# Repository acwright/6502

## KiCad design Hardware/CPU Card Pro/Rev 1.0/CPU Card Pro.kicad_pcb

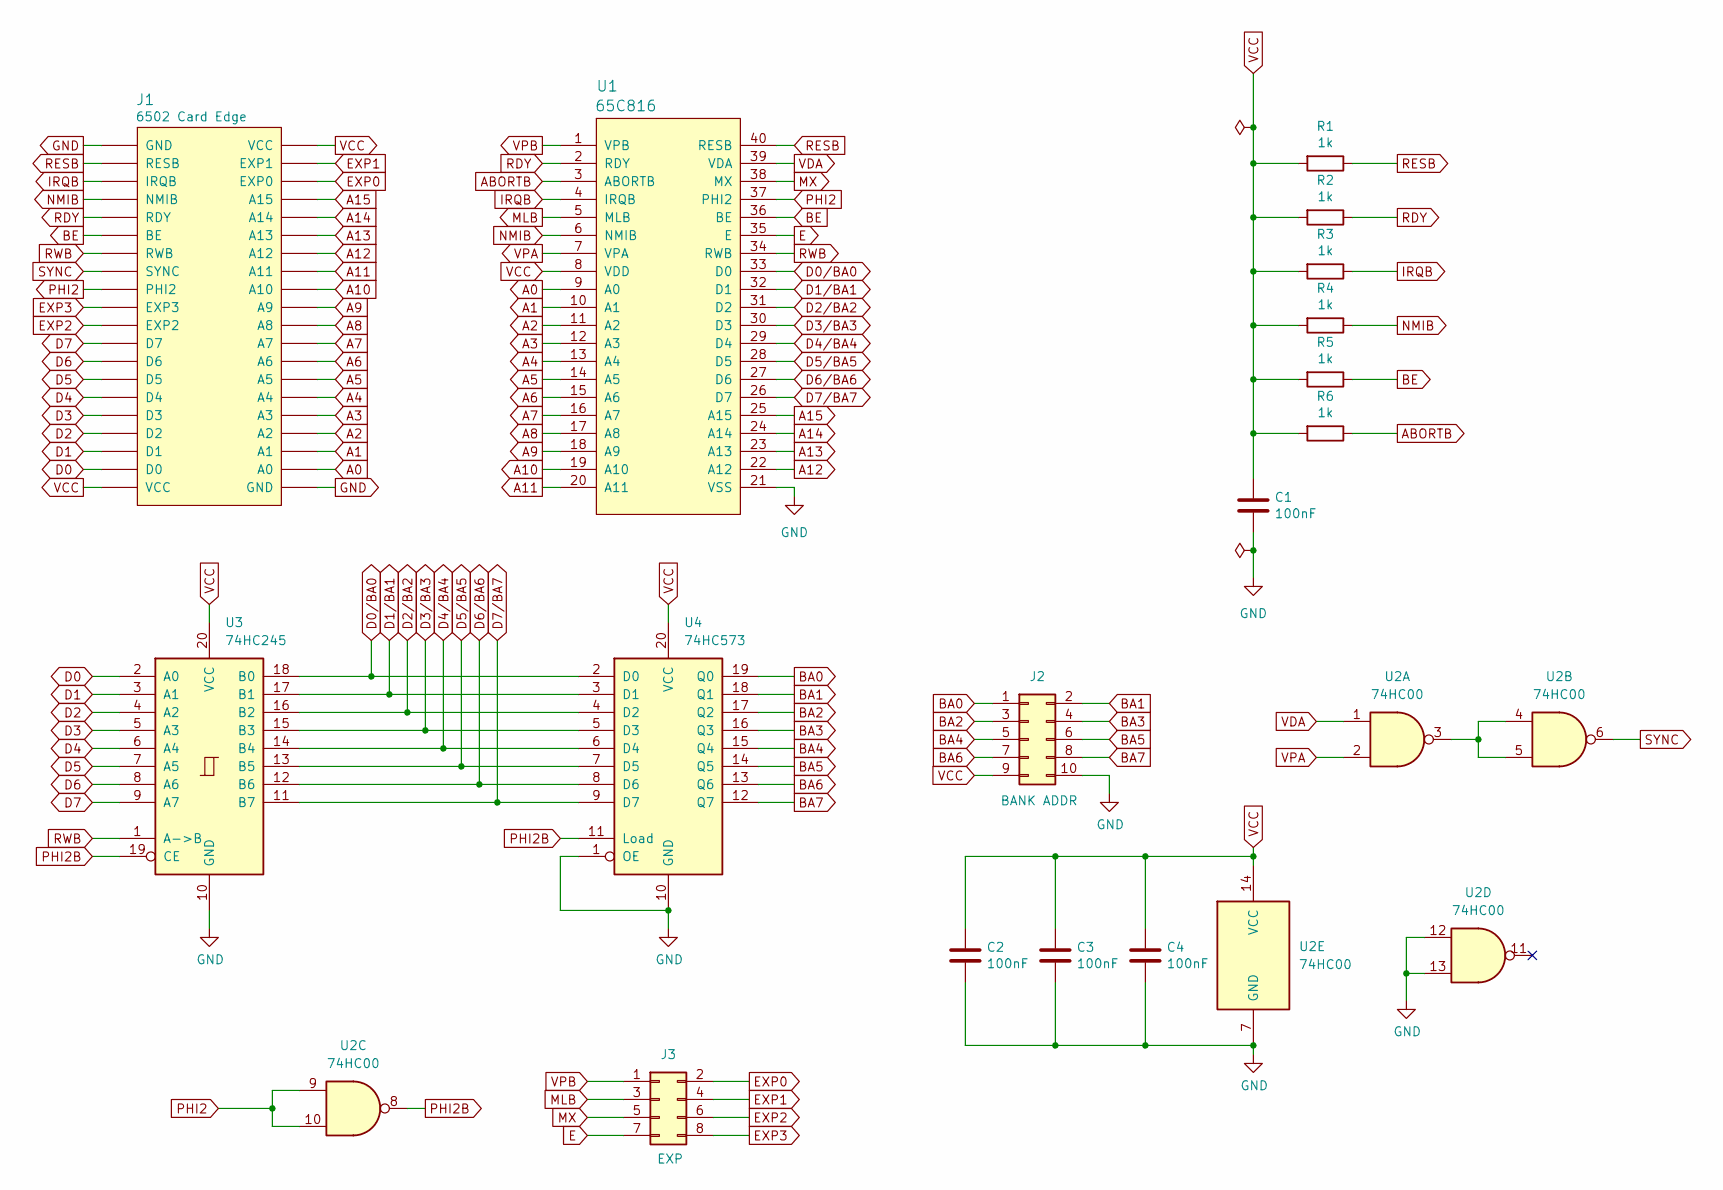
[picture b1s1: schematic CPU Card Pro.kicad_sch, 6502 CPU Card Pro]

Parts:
C1, C2, C3, C4: 100nF; C_0805_2012Metric; LCSC C49678
J1: 6502 Card Edge
J2: BANK ADDR; PinHeader_2x05_P2.54mm_Vertical
J3: EXP; PinHeader_2x04_P2.54mm_Vertical
R1, R2, R3, R4, R5, R6: 1k; R_0805_2012Metric; LCSC C17513
U1: 65C816; DIP-40_W15.24mm_Socket_LongPads
U2: 74HC00; SOIC-14_3.9x8.7mm_P1.27mm; LCSC C5586
U3: 74HC245; TSSOP-20_4.4x6.5mm_P0.65mm; LCSC C5626
U4: 74HC573; SOIC-20W_7.5x12.8mm_P1.27mm; LCSC C5608

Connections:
A0: J1.A0, U1.9 (A0)
A1: J1.A1, U1.10 (A1)
A2: J1.A2, U1.11 (A2)
A3: J1.A3, U1.12 (A3)
A4: J1.A4, U1.13 (A4)
A5: J1.A5, U1.14 (A5)
A6: J1.A6, U1.15 (A6)
A7: J1.A7, U1.16 (A7)
A8: J1.A8, U1.17 (A8)
A9: J1.A9, U1.18 (A9)
A10: J1.A10, U1.19 (A10)
A11: J1.A11, U1.20 (A11)
A12: J1.A12, U1.22 (A12)
A13: J1.A13, U1.23 (A13)
A14: J1.A14, U1.24 (A14)
A15: J1.A15, U1.25 (A15)
ABORTB: R6.1, U1.3 (ABORTB)
BA0: J2.1, U4.19 (Q0)
BA1: J2.2, U4.18 (Q1)
BA2: J2.3, U4.17 (Q2)
BA3: J2.4, U4.16 (Q3)
BA4: J2.5, U4.15 (Q4)
BA5: J2.6, U4.14 (Q5)
BA6: J2.7, U4.13 (Q6)
BA7: J2.8, U4.12 (Q7)
BE: J1.BE, R5.1, U1.36 (BE)
D0: J1.D0, U3.2 (A0)
D0/BA0: U1.33 (D0), U3.18 (B0), U4.2 (D0)
D1: J1.D1, U3.3 (A1)
D1/BA1: U1.32 (D1), U3.17 (B1), U4.3 (D1)
D2: J1.D2, U3.4 (A2)
D2/BA2: U1.31 (D2), U3.16 (B2), U4.4 (D2)
D3: J1.D3, U3.5 (A3)
D3/BA3: U1.30 (D3), U3.15 (B3), U4.5 (D3)
D4: J1.D4, U3.6 (A4)
D4/BA4: U1.29 (D4), U3.14 (B4), U4.6 (D4)
D5: J1.D5, U3.7 (A5)
D5/BA5: U1.28 (D5), U3.13 (B5), U4.7 (D5)
D6: J1.D6, U3.8 (A6)
D6/BA6: U1.27 (D6), U3.12 (B6), U4.8 (D6)
D7: J1.D7, U3.9 (A7)
D7/BA7: U1.26 (D7), U3.11 (B7), U4.9 (D7)
E: J3.7, U1.35 (E)
EXP0: J1.EXP0, J3.2
EXP1: J1.EXP1, J3.4
EXP2: J1.EXP2, J3.6
EXP3: J1.EXP3, J3.8
GND: C1.2, C2.2, C3.2, C4.2, J1.GND, J2.10, U1.21 (VSS), U2.7 (GND), U2.12, U2.13, U3.10 (GND), U4.1 (OE), U4.10 (GND)
IRQB: J1.IRQB, R3.1, U1.4 (IRQB)
MLB: J3.3, U1.5 (MLB)
MX: J3.5, U1.38 (MX)
NMIB: J1.NMIB, R4.1, U1.6 (NMIB)
unnamed: U2.3, U2.4, U2.5
PHI2: J1.PHI2, U1.37 (PHI2), U2.9, U2.10
PHI2B: U2.8, U3.19 (CE), U4.11 (Load)
RDY: J1.RDY, R2.1, U1.2 (RDY)
RESB: J1.RESB, R1.1, U1.40 (RESB)
RWB: J1.RWB, U1.34 (RWB), U3.1 (A->B)
SYNC: J1.SYNC, U2.6
VCC: C1.1, C2.1, C3.1, C4.1, J1.VCC, J2.9, R1.2, R2.2, R3.2, R4.2, R5.2, R6.2, U1.8 (VDD), U2.14 (VCC), U3.20 (VCC), U4.20 (VCC)
VDA: U1.39 (VDA), U2.1
VPA: U1.7 (VPA), U2.2
VPB: J3.1, U1.1 (VPB)

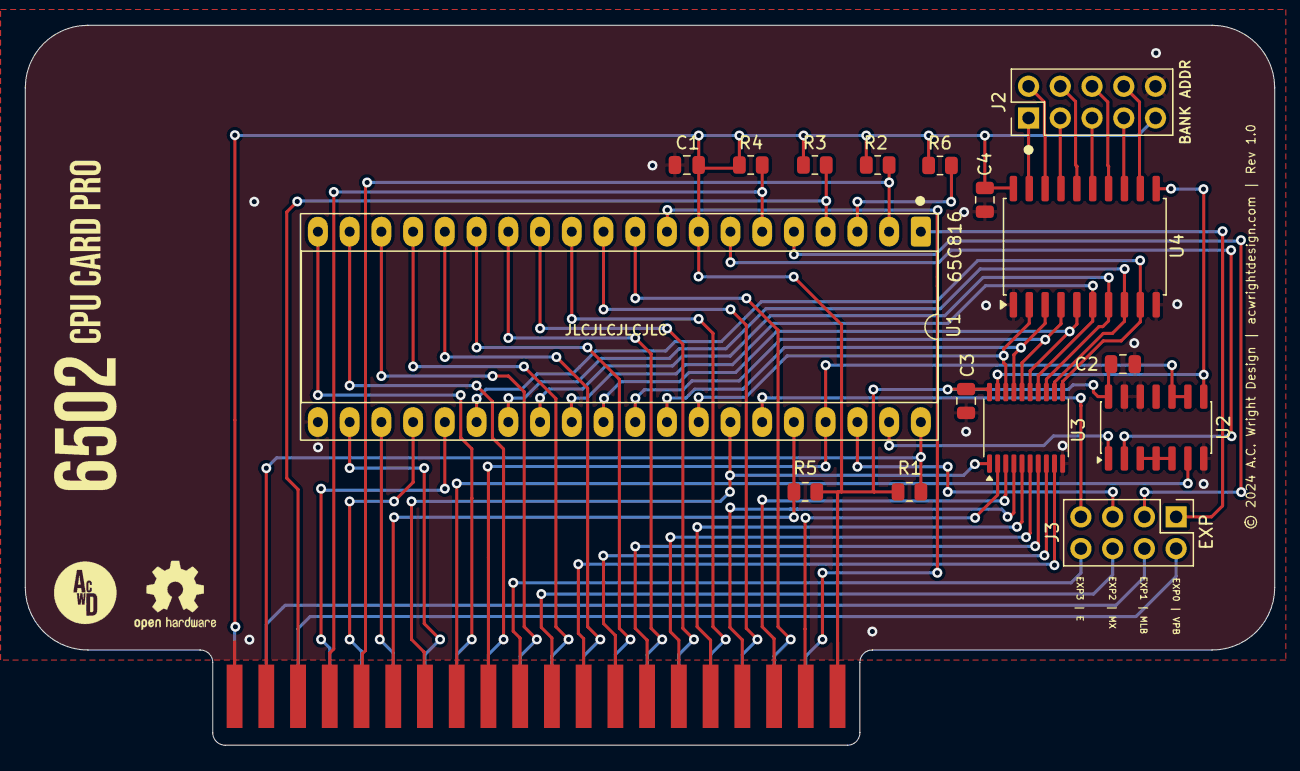
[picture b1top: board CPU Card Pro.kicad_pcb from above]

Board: 2 copper layers, 100.0 x 57.6 mm, 17 parts (0 on the bottom side), 63 nets.

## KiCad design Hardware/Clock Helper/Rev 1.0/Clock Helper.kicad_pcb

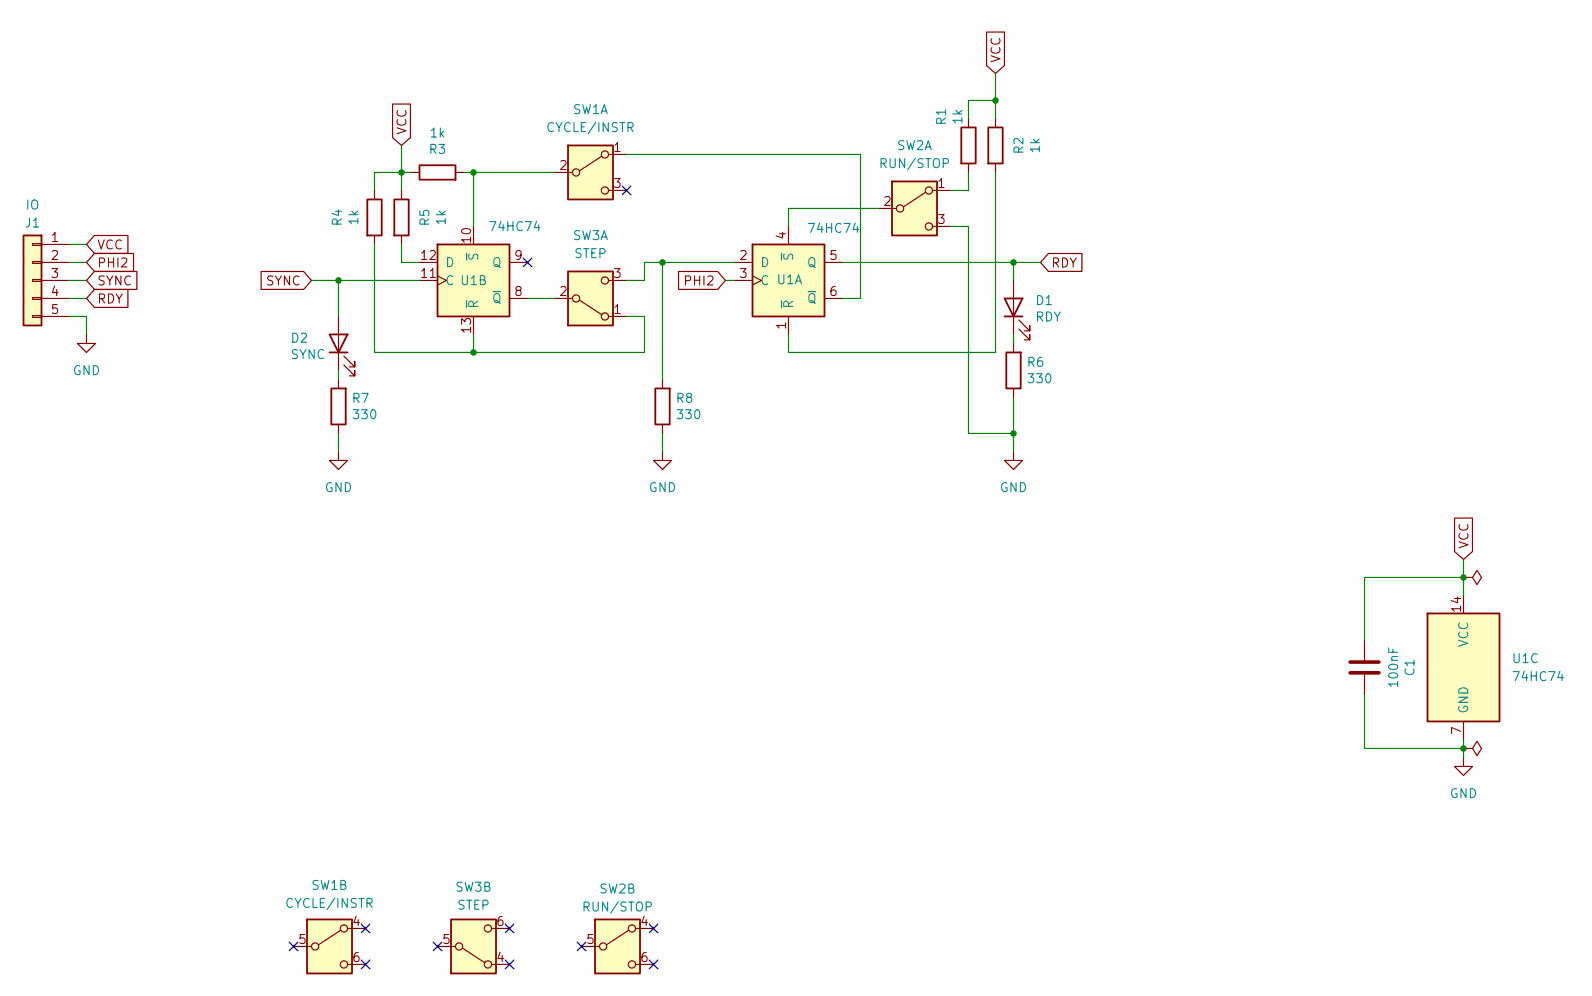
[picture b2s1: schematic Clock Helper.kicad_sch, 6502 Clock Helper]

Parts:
C1: 100nF; C_Disc_D5.0mm_W2.5mm_P2.50mm; LCSC C49678
D1: RDY; LED_D3.0mm
D2: SYNC; LED_D3.0mm
J1: IO; PinHeader_1x05_P2.54mm_Vertical
R1, R2: 1k; R_Axial_DIN0204_L3.6mm_D1.6mm_P5.08mm_Horizontal
R3, R4, R5: 1k; R_Axial_DIN0204_L3.6mm_D1.6mm_P5.08mm_Horizontal; LCSC C17513
R6, R7, R8: 330; R_Axial_DIN0204_L3.6mm_D1.6mm_P5.08mm_Horizontal
SW1: CYCLE/INSTR; XKB5858; MPN XKB5858-Z
SW2: RUN/STOP; XKB5858; MPN XKB5858-Z
SW3: STEP; XKB5858; MPN XKB5858-W
U1: 74HC74; DIP-14_W7.62mm_Socket_LongPads

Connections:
GND: C1.2, J1.5, R6.1, R7.1, R8.1, SW2.3 (C), U1.7 (GND)
unnamed: D1.1 (K), R6.2
unnamed: D2.1 (K), R7.2
unnamed: SW1.1 (A), U1.6 (~Q)
unnamed: R3.2, SW1.2 (B), U1.10 (~S)
unnamed: R1.2, SW2.1 (A)
unnamed: SW2.2 (B), U1.4 (~S)
unnamed: R4.2, SW3.1 (A), U1.13 (~R)
unnamed: SW3.2 (B), U1.8 (~Q)
unnamed: R8.2, SW3.3 (C), U1.2 (D)
unnamed: R2.2, U1.1 (~R)
unnamed: R5.2, U1.12 (D)
PHI2: J1.2, U1.3 (C)
RDY: D1.2 (A), J1.4, U1.5 (Q)
SYNC: D2.2 (A), J1.3, U1.11 (C)
VCC: C1.1, J1.1, R1.1, R2.1, R3.1, R4.1, R5.1, U1.14 (VCC)

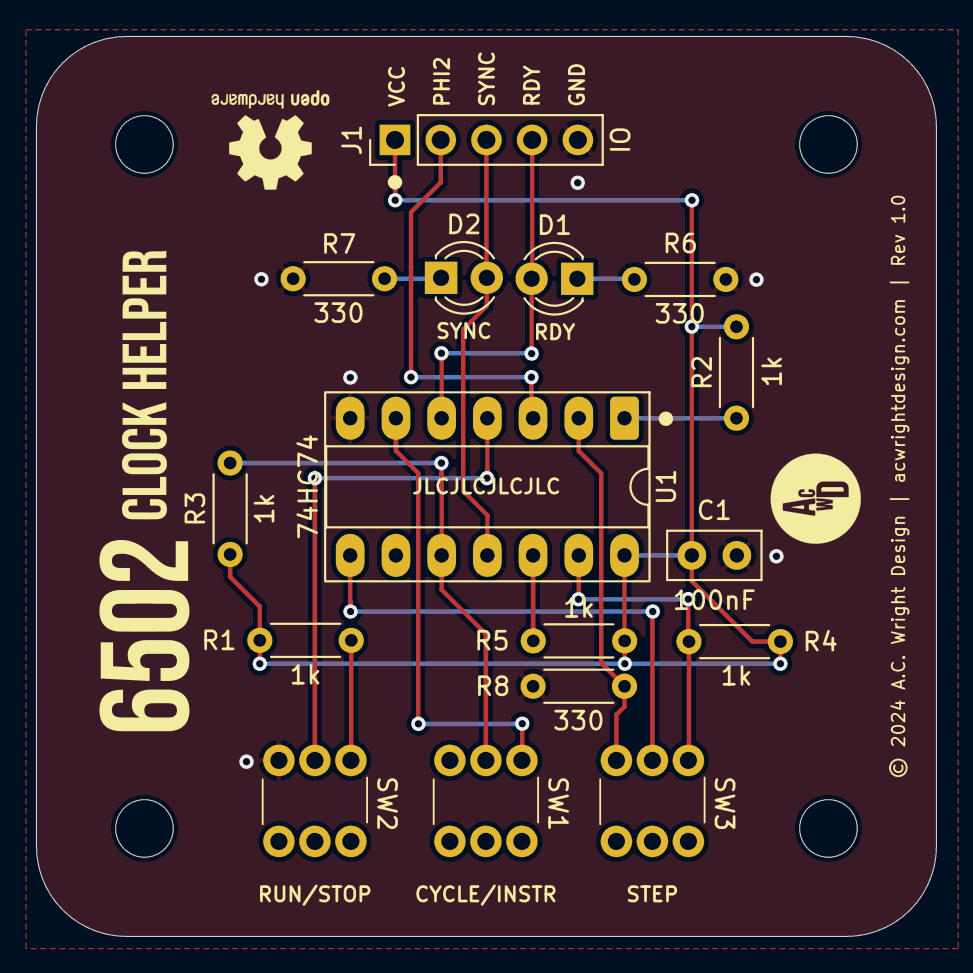
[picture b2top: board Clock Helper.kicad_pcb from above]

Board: 2 copper layers, 50.0 x 50.0 mm, 20 parts (0 on the bottom side), 16 nets.

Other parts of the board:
H1, H2, H3, H4: MountingHole; MountingHole_3.2mm_M3

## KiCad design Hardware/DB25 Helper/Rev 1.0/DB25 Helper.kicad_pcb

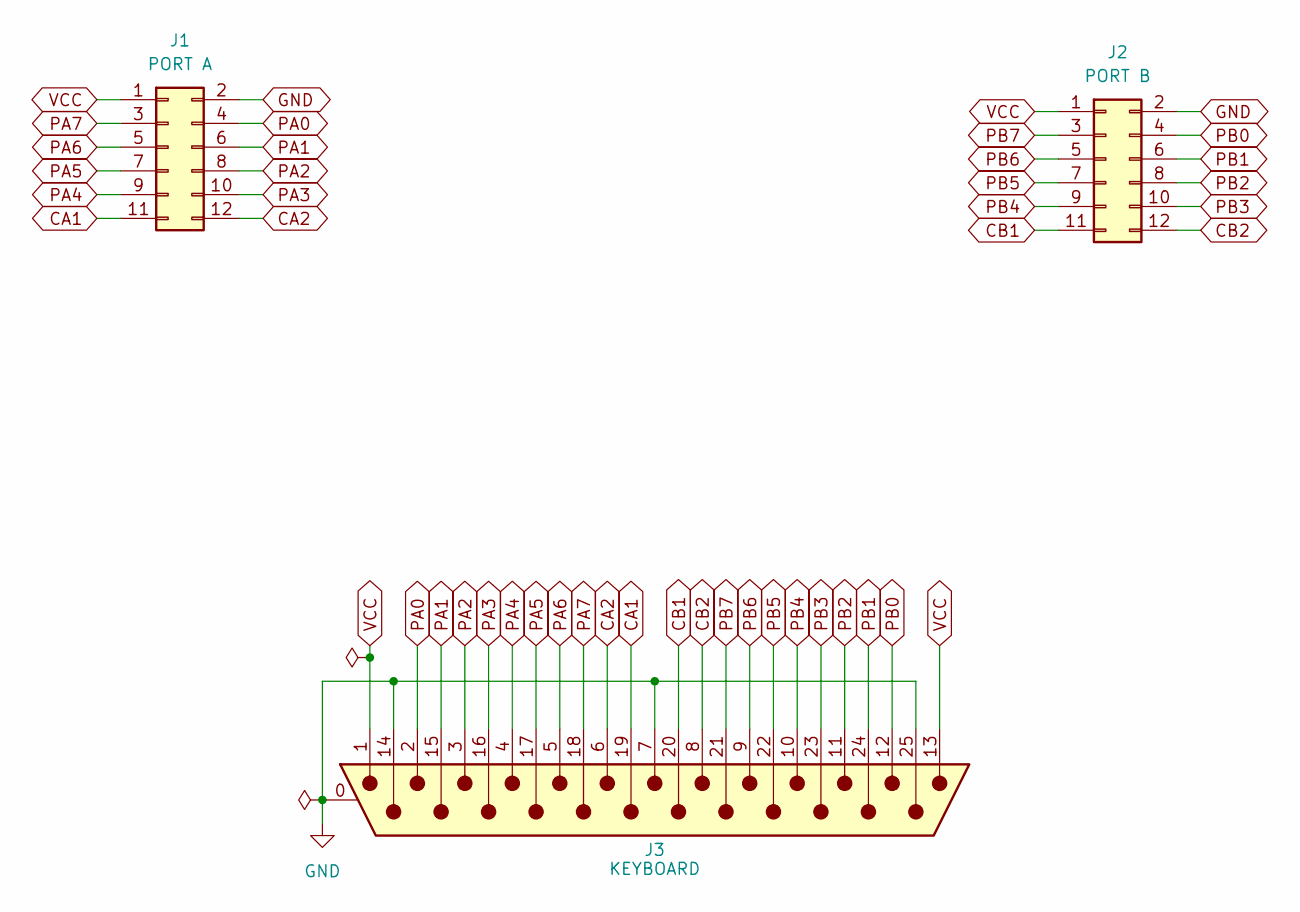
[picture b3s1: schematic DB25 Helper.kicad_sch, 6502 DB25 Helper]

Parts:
J1: PORT A; 6502 GPIO Connector
J2: PORT B; 6502 GPIO Connector
J3: KEYBOARD; DSUB-25_Pins_Horizontal_P2.77x2.84mm_EdgePinOffset7.70mm_Ho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; MPN D25P33E4GX00LF; Digikey 609-1505-ND

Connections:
CA1: J1.11, J3.19
CA2: J1.12, J3.6
CB1: J2.11, J3.20
CB2: J2.12, J3.8
GND: J1.2, J2.2, J3.0 (PAD), J3.7, J3.14, J3.25
PA0: J1.4, J3.2
PA1: J1.6, J3.15
PA2: J1.8, J3.3
PA3: J1.10, J3.16
PA4: J1.9, J3.4
PA5: J1.7, J3.17
PA6: J1.5, J3.5
PA7: J1.3, J3.18
PB0: J2.4, J3.12
PB1: J2.6, J3.24
PB2: J2.8, J3.11
PB3: J2.10, J3.23
PB4: J2.9, J3.10
PB5: J2.7, J3.22
PB6: J2.5, J3.9
PB7: J2.3, J3.21
VCC: J1.1, J2.1, J3.1, J3.13

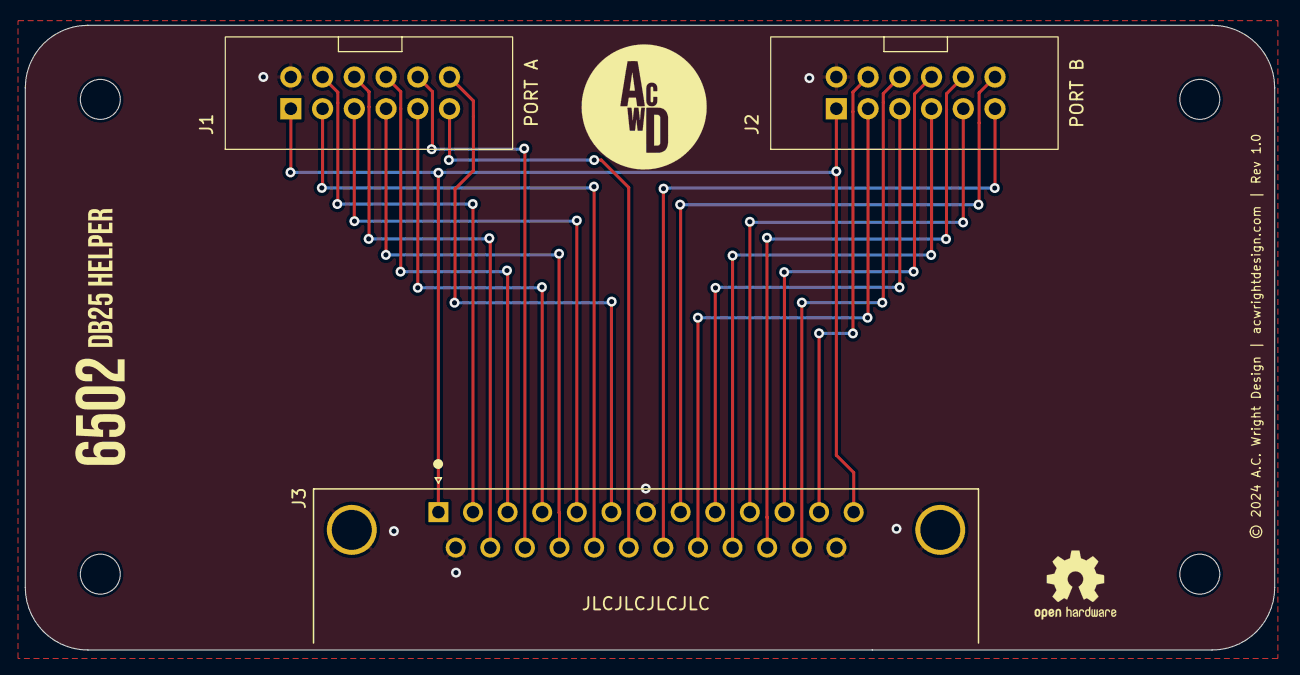
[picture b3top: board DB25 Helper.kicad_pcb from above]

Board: 2 copper layers, 100.0 x 50.0 mm, 7 parts (0 on the bottom side), 22 nets.

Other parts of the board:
H1, H2, H3, H4: MountingHole; MountingHole_3.2mm_M3

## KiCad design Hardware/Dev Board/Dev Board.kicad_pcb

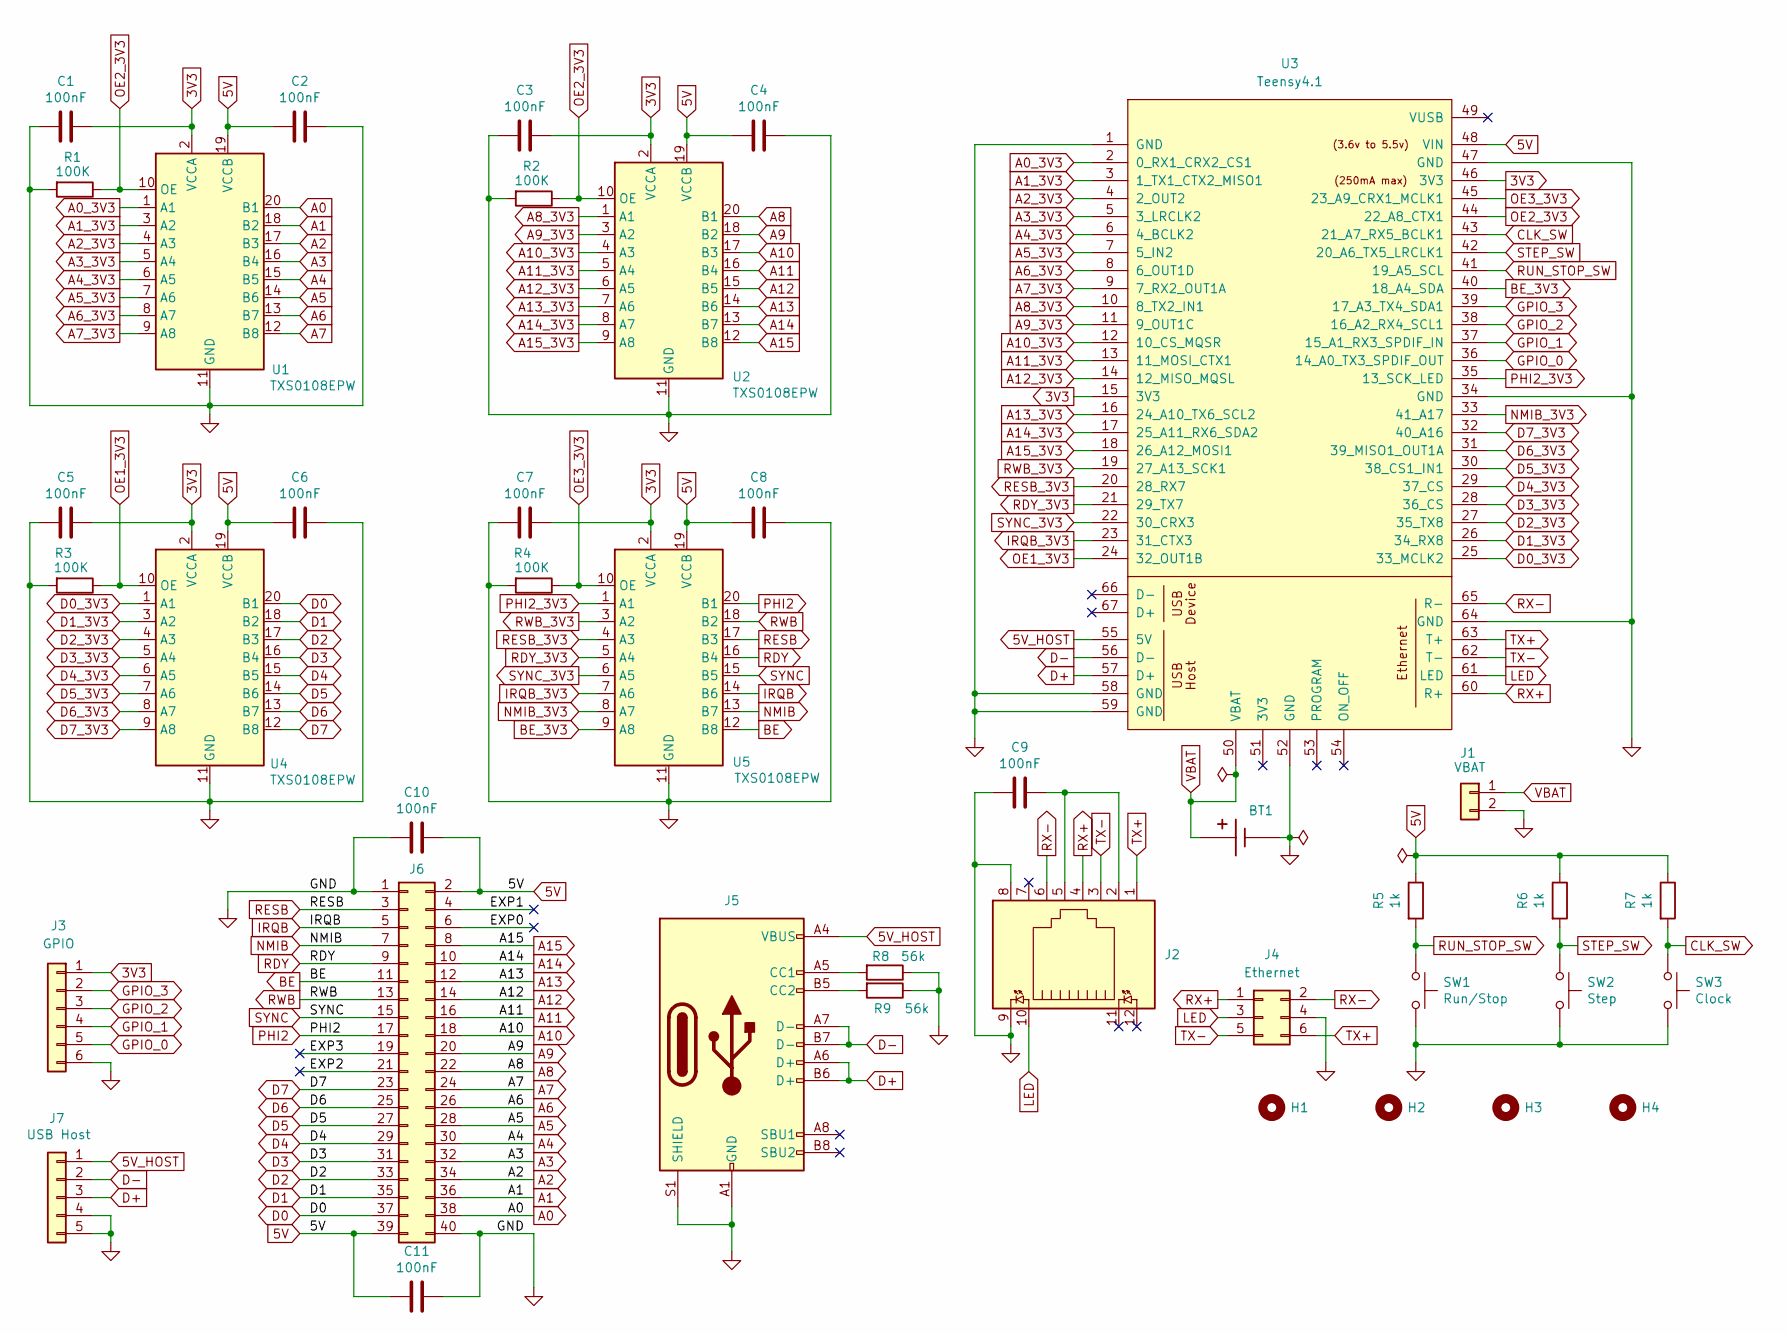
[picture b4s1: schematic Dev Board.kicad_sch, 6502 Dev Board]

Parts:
BT1: BAT-HLD-001-THM; BAT_BAT-HLD-001-THM
C1, C2, C3, C4, C5, C6, C7, C8, C9, C10, C11: 100nF; C_0805_2012Metric; LCSC C49678
H1, H2, H3, H4: MountingHole; MountingHole_3.2mm_M3
J1: VBAT; PinHeader_1x02_P2.54mm_Vertical
J2: RJ45_LED; J1B1211CCD; MPN J1B1211CCD
J3: GPIO; PinHeader_1x06_P2.54mm_Horizontal
J4: Ethernet; PinHeader_2x03_P2.00mm_Vertical
J5: USB_C_Receptacle_USB2.0; USB_C_Receptacle_HRO_TYPE-C-31-M-12; LCSC C2988369
J6: Conn_02x20_Odd_Even; PinHeader_2x20_P2.54mm_Vertical
J7: USB Host; PinHeader_1x05_P2.54mm_Vertical
R1, R2, R3, R4: 100K; R_0805_2012Metric; LCSC C149504
R5, R6, R7: 1k; R_0805_2012Metric; LCSC C17513
R8, R9: 56k; R_0805_2012Metric; LCSC C169923
SW1: Run/Stop; SW_TS-1187A-B-A-B; LCSC C318884
SW2: Step; SW_TS-1187A-B-A-B; LCSC C318884
SW3: Clock; SW_TS-1187A-B-A-B; LCSC C318884
U1, U2, U4, U5: TXS0108EPW; TSSOP-20_4.4x6.5mm_P0.65mm; LCSC C17206
U3: Teensy4.1; Teensy41

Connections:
3V3: C1.1, C3.1, C5.1, C7.1, J3.1, U1.2 (VCCA), U2.2 (VCCA), U3.15 (3V3), U3.46 (3V3), U4.2 (VCCA), U5.2 (VCCA)
5V: C2.2, C4.2, C6.2, C8.2, C10.1, C11.2, J6.2, J6.39, R5.1, R6.1, R7.1, U1.19 (VCCB), U2.19 (VCCB), U3.48 (VIN), U4.19 (VCCB), U5.19 (VCCB)
5V_HOST: J5.A4 (VBUS), J5.A9 (VBUS), J5.B4 (VBUS), J5.B9 (VBUS), J7.1, U3.55 (5V)
/EXP0: J6.6
/EXP1: J6.4
/EXP2: J6.21
/EXP3: J6.19
A0: J6.38, U1.20 (B1)
A0_3V3: U1.1 (A1), U3.2 (0_RX1_CRX2_CS1)
A1: J6.36, U1.18 (B2)
A1_3V3: U1.3 (A2), U3.3 (1_TX1_CTX2_MISO1)
A2: J6.34, U1.17 (B3)
A2_3V3: U1.4 (A3), U3.4 (2_OUT2)
A3: J6.32, U1.16 (B4)
A3_3V3: U1.5 (A4), U3.5 (3_LRCLK2)
A4: J6.30, U1.15 (B5)
A4_3V3: U1.6 (A5), U3.6 (4_BCLK2)
A5: J6.28, U1.14 (B6)
A5_3V3: U1.7 (A6), U3.7 (5_IN2)
A6: J6.26, U1.13 (B7)
A6_3V3: U1.8 (A7), U3.8 (6_OUT1D)
A7: J6.24, U1.12 (B8)
A7_3V3: U1.9 (A8), U3.9 (7_RX2_OUT1A)
A8: J6.22, U2.20 (B1)
A8_3V3: U2.1 (A1), U3.10 (8_TX2_IN1)
A9: J6.20, U2.18 (B2)
A9_3V3: U2.3 (A2), U3.11 (9_OUT1C)
A10: J6.18, U2.17 (B3)
A10_3V3: U2.4 (A3), U3.12 (10_CS_MQSR)
A11: J6.16, U2.16 (B4)
A11_3V3: U2.5 (A4), U3.13 (11_MOSI_CTX1)
A12: J6.14, U2.15 (B5)
A12_3V3: U2.6 (A5), U3.14 (12_MISO_MQSL)
A13: J6.12, U2.14 (B6)
A13_3V3: U2.7 (A6), U3.16 (24_A10_TX6_SCL2)
A14: J6.10, U2.13 (B7)
A14_3V3: U2.8 (A7), U3.17 (25_A11_RX6_SDA2)
A15: J6.8, U2.12 (B8)
A15_3V3: U2.9 (A8), U3.18 (26_A12_MOSI1)
BE: J6.11, U5.12 (B8)
BE_3V3: U3.40 (18_A4_SDA), U5.9 (A8)
CLK_SW: R7.2, SW3.1, U3.43 (21_A7_RX5_BCLK1)
D0: J6.37, U4.20 (B1)
D0_3V3: U3.25 (33_MCLK2), U4.1 (A1)
D1: J6.35, U4.18 (B2)
D1_3V3: U3.26 (34_RX8), U4.3 (A2)
D2: J6.33, U4.17 (B3)
D2_3V3: U3.27 (35_TX8), U4.4 (A3)
D3: J6.31, U4.16 (B4)
D3_3V3: U3.28 (36_CS), U4.5 (A4)
D4: J6.29, U4.15 (B5)
D4_3V3: U3.29 (37_CS), U4.6 (A5)
D5: J6.27, U4.14 (B6)
D5_3V3: U3.30 (38_CS1_IN1), U4.7 (A6)
D6: J6.25, U4.13 (B7)
D6_3V3: U3.31 (39_MISO1_OUT1A), U4.8 (A7)
D7: J6.23, U4.12 (B8)
D7_3V3: U3.32 (40_A16), U4.9 (A8)
D+: J5.A6 (D+), J5.B6 (D+), J7.3, U3.57 (D+)
D-: J5.A7 (D-), J5.B7 (D-), J7.2, U3.56 (D-)
GND: BT1.-, C1.2, C2.1, C3.2, C4.1, C5.2, C6.1, C7.2, C8.1, C9.2, C10.2, C11.1, J1.2, J2.8, J2.9, J3.6, J4.4, J5.A1 (GND), J5.A12 (GND), J5.B1 (GND), J5.B12 (GND), J5.S1 (SHIELD), J6.1, J6.40, J7.4, J7.5, R1.2, R2.2, R3.2, R4.2, R8.1, R9.1, SW1.2, SW2.2, SW3.2, U1.11 (GND), U2.11 (GND), U3.1 (GND), U3.34 (GND), U3.47 (GND), U3.52 (GND), U3.58 (GND), U3.59 (GND), U3.64 (GND), U4.11 (GND), U5.11 (GND)
GPIO_0: J3.5, U3.36 (14_A0_TX3_SPDIF_OUT)
GPIO_1: J3.4, U3.37 (15_A1_RX3_SPDIF_IN)
GPIO_2: J3.3, U3.38 (16_A2_RX4_SCL1)
GPIO_3: J3.2, U3.39 (17_A3_TX4_SDA1)
IRQB: J6.5, U5.14 (B6)
IRQB_3V3: U3.23 (31_CTX3), U5.7 (A6)
LED: J2.10, J4.3, U3.61 (LED)
NMIB: J6.7, U5.13 (B7)
NMIB_3V3: U3.33 (41_A17), U5.8 (A7)
unnamed: C9.1, J2.2, J2.5
unnamed: J5.A5 (CC1), R8.2
unnamed: J5.B5 (CC2), R9.2
OE1_3V3: R3.1, U3.24 (32_OUT1B), U4.10 (OE)
OE2_3V3: R1.1, R2.1, U1.10 (OE), U2.10 (OE), U3.44 (22_A8_CTX1)
OE3_3V3: R4.1, U3.45 (23_A9_CRX1_MCLK1), U5.10 (OE)
PHI2: J6.17, U5.20 (B1)
PHI2_3V3: U3.35 (13_SCK_LED), U5.1 (A1)
RDY: J6.9, U5.16 (B4)
RDY_3V3: U3.21 (29_TX7), U5.5 (A4)
RESB: J6.3, U5.17 (B3)
RESB_3V3: U3.20 (28_RX7), U5.4 (A3)
RUN_STOP_SW: R5.2, SW1.1, U3.41 (19_A5_SCL)
RWB: J6.13, U5.18 (B2)
RWB_3V3: U3.19 (27_A13_SCK1), U5.3 (A2)
RX+: J2.4, J4.1, U3.60 (R+)
RX-: J2.6, J4.2, U3.65 (R-)
STEP_SW: R6.2, SW2.1, U3.42 (20_A6_TX5_LRCLK1)
SYNC: J6.15, U5.15 (B5)
SYNC_3V3: U3.22 (30_CRX3), U5.6 (A5)
TX+: J2.1, J4.6, U3.63 (T+)
TX-: J2.3, J4.5, U3.62 (T-)
VBAT: BT1.+, J1.1, U3.50 (VBAT)

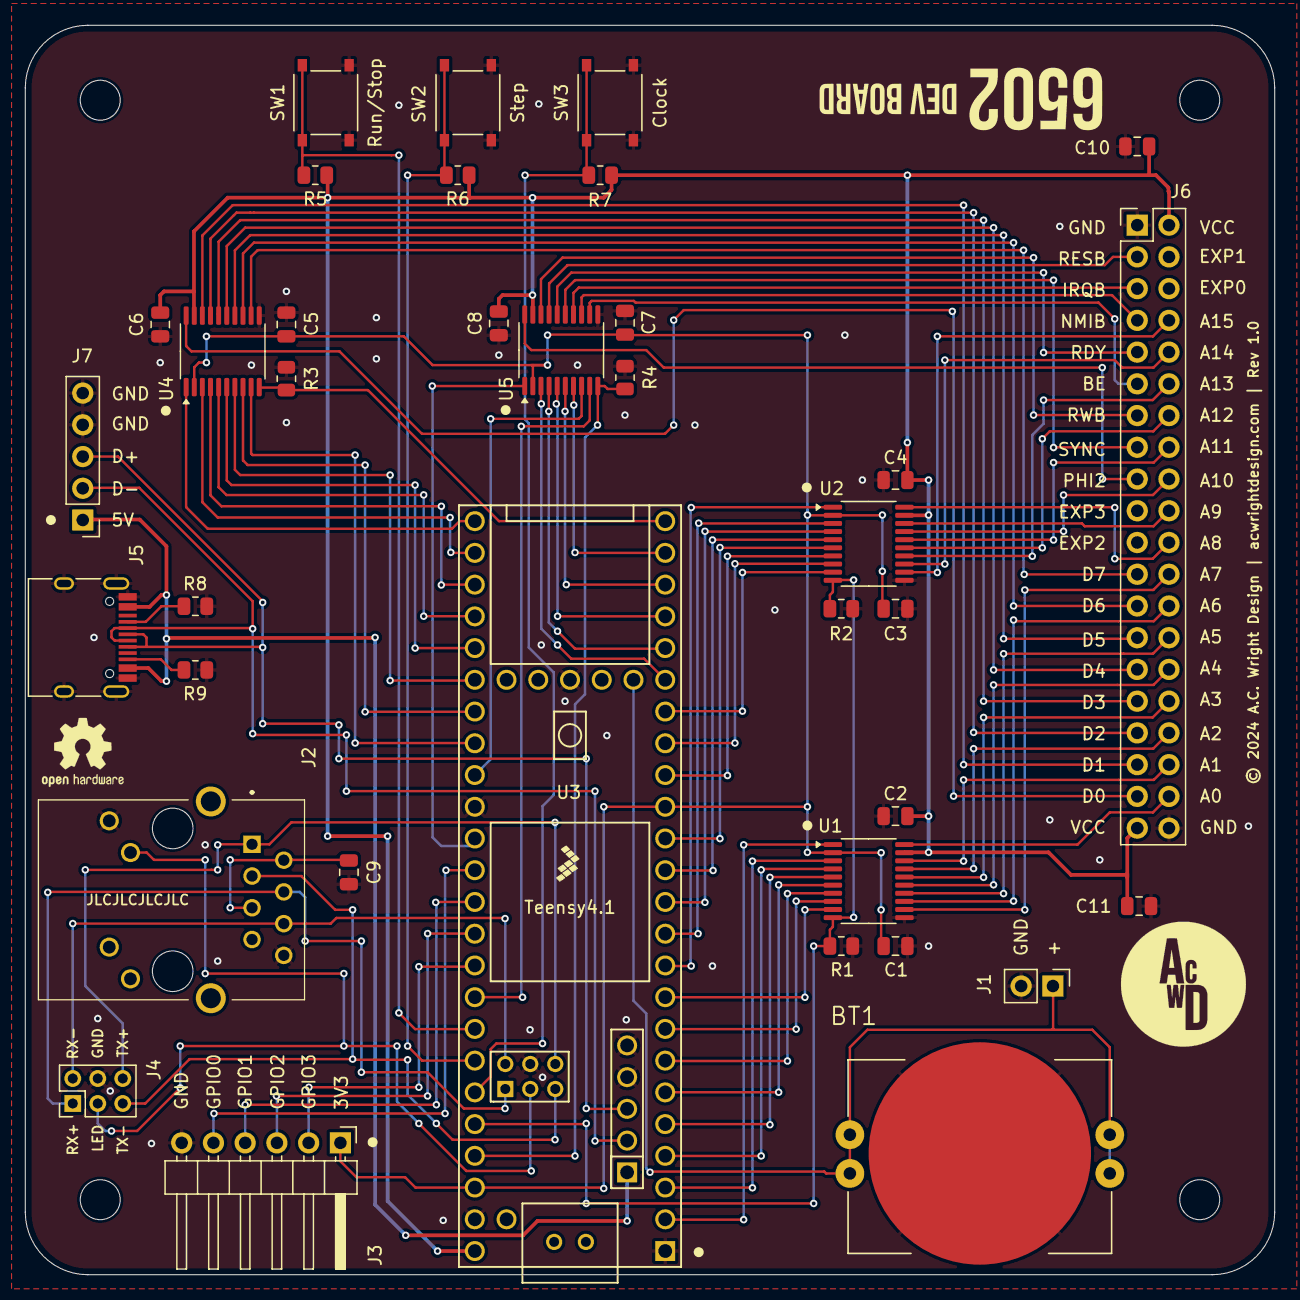
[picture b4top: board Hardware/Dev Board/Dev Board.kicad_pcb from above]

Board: 2 copper layers, 100.0 x 100.0 mm, 40 parts (0 on the bottom side), 89 nets.

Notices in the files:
Hardware/CPU Card Pro/Rev 1.0/CPU Card Pro.kicad_pcb:
© 2024 A.C. Wright Design | acwrightdesign.com | Rev 1.0
